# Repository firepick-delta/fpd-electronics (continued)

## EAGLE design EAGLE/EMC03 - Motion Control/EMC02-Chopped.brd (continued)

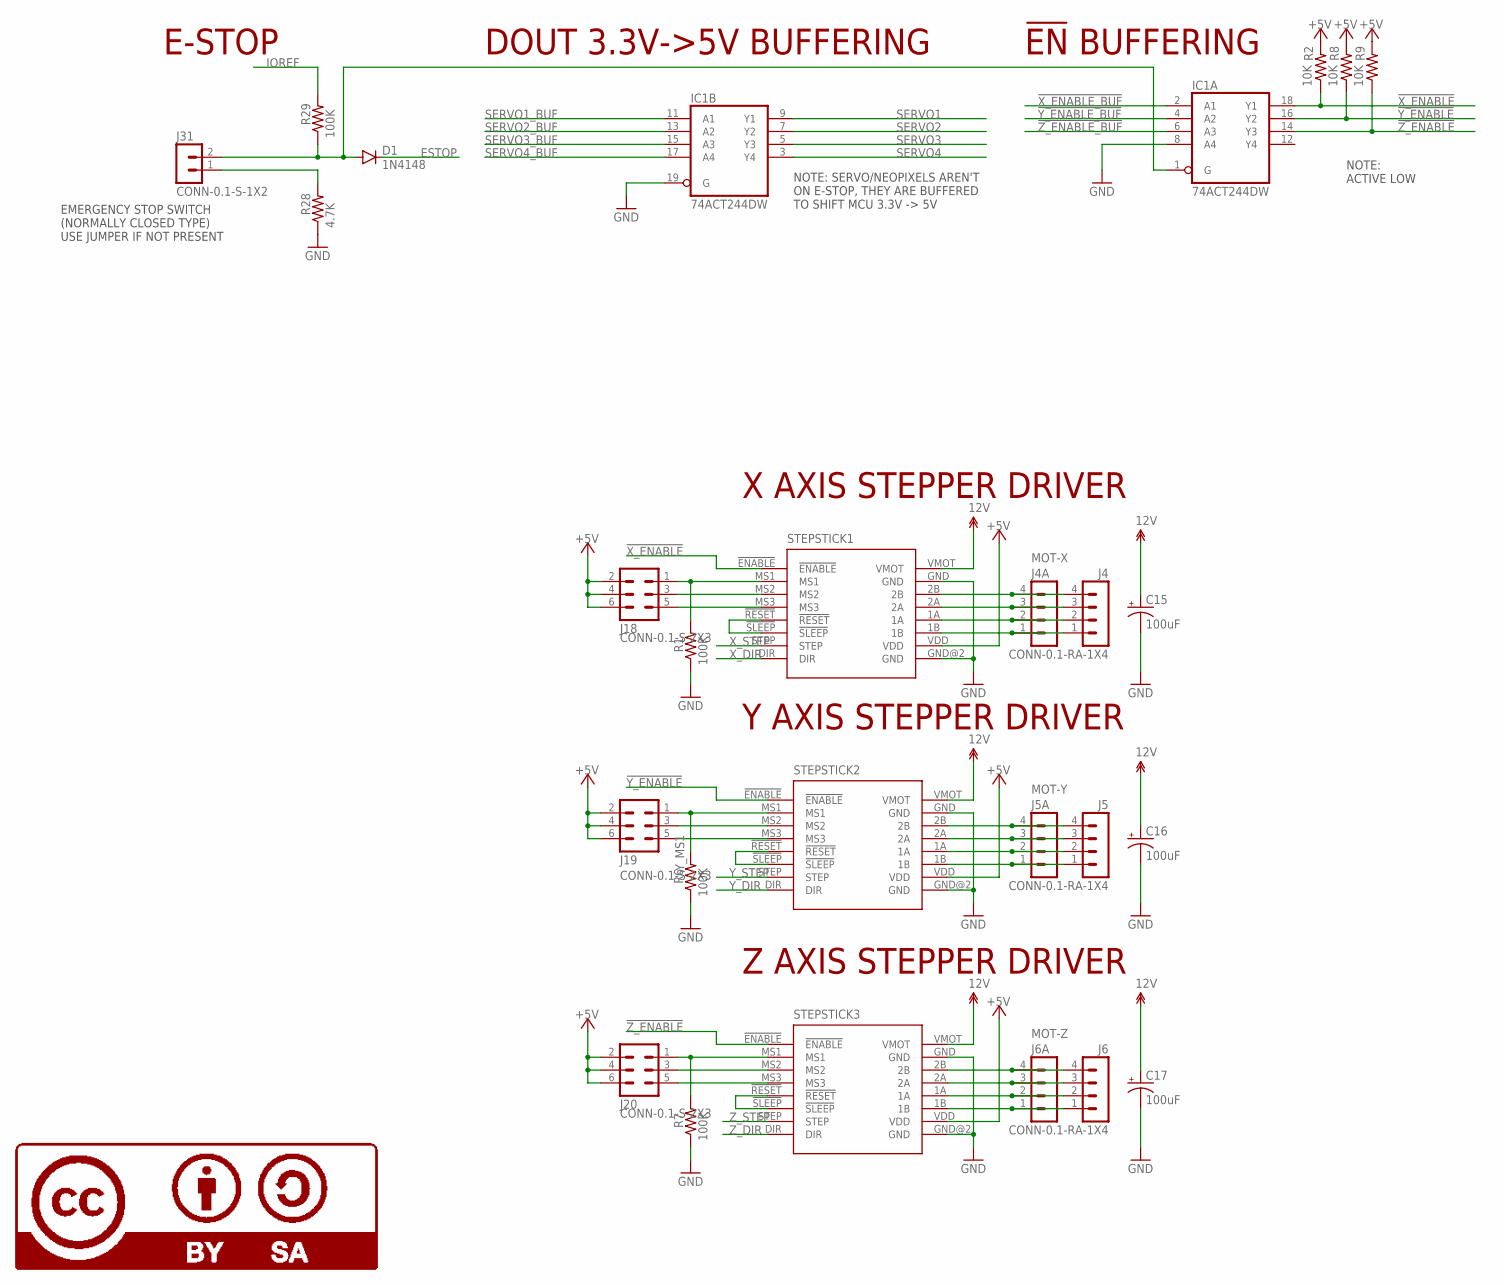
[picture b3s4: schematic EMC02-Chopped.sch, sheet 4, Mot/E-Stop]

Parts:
C15, C16, C17: 100uF; PANASONIC_D; PARTNO 25TXV100M6.3X8
D1: 1N4148; SOD-123; PARTNO 1N4148W-7-F
IC1: 74ACT244DW; SO20W; PARTNO 74ACT244SCX
J4, J5, J6: CONN-0.1-RA-1X4; MA04-1; PARTNO CONN-0.1-RA-1X4
J4A: MOT-X; CONN-JST-PH_2.0MM_4PIN-SMT-RA
J5A: MOT-Y; CONN-JST-PH_2.0MM_4PIN-SMT-RA
J6A: MOT-Z; CONN-JST-PH_2.0MM_4PIN-SMT-RA
J18, J19, J20: CONN-0.1-S-2X3; MA03-2; PARTNO CONN-0.1-S-2X3
J31: CONN-0.1-S-1X2; MA02-1; PARTNO CONN-0.1-S-1X2
LOGO7: LOGO-CC-BY-SALARGE; LOGO-CC-BY-SA
R1, R6, R7, R29: 100K; 0805; PARTNO RC0805FR-07100KL
R2, R8, R9: 10K; 0805; PARTNO RC0805FR-0710KL
R28: 4.7K; 0805; PARTNO RC0805FR-074K7L
STEPSTICK1, STEPSTICK2, STEPSTICK3: STEPSTICK; PARTNO PPPC081LFBN-RC

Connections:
12V: C15.+, C16.+, C17.+, STEPSTICK1.VMOT, STEPSTICK2.VMOT, STEPSTICK3.VMOT; also elsewhere on the board
!X_ENABLE: IC1.18 (Y1), R2.1, STEPSTICK1.!ENABLE!
!X_ENABLE_BUF: IC1.2 (A1)
!Y_ENABLE: IC1.16 (Y2), R8.1, STEPSTICK2.!ENABLE!
!Y_ENABLE_BUF: IC1.4 (A2)
!Z_ENABLE: IC1.14 (Y3), R9.1, STEPSTICK3.!ENABLE!
!Z_ENABLE_BUF: IC1.6 (A3)
+5V: J18.2, J18.4, J18.6, J19.2, J19.4, J19.6, J20.2, J20.4, J20.6, R2.2, R8.2, R9.2, STEPSTICK1.VDD, STEPSTICK2.VDD, STEPSTICK3.VDD; also elsewhere on the board
ESTOP: D1.C
ESTOP_OE: D1.A, IC1.1 (G), J31.2, R29.1
GND: C15.-, C16.-, C17.-, IC1.8 (A4), IC1.19 (G), R1.1, R6.1, R7.1, R28.1, STEPSTICK1.GND, STEPSTICK1.GND@2 (GND), STEPSTICK2.GND, STEPSTICK2.GND@2 (GND), STEPSTICK3.GND, STEPSTICK3.GND@2 (GND); also elsewhere on the board
IOREF: R29.2
unnamed: J31.1, R28.2
unnamed: STEPSTICK1.!RESET!, STEPSTICK1.!SLEEP!
unnamed: STEPSTICK2.!RESET!, STEPSTICK2.!SLEEP!
unnamed: STEPSTICK3.!RESET!, STEPSTICK3.!SLEEP!
SERVO1: IC1.9 (Y1); also elsewhere on the board
SERVO1_BUF: IC1.11 (A1)
SERVO2: IC1.7 (Y2); also elsewhere on the board
SERVO2_BUF: IC1.13 (A2)
SERVO3: IC1.5 (Y3); also elsewhere on the board
SERVO3_BUF: IC1.15 (A3)
SERVO4: IC1.3 (Y4); also elsewhere on the board
SERVO4_BUF: IC1.17 (A4)
X1A: J4.2, J4A.2, STEPSTICK1.1A
X1B: J4.1, J4A.1, STEPSTICK1.1B
X2A: J4.3, J4A.3, STEPSTICK1.2A
X2B: J4.4, J4A.4, STEPSTICK1.2B
X_DIR: STEPSTICK1.DIR
X_MS1: J18.1, R1.2, STEPSTICK1.MS1
X_MS2: J18.3, STEPSTICK1.MS2
X_MS3: J18.5, STEPSTICK1.MS3
X_STEP: STEPSTICK1.STEP
Y1A: J5.2, J5A.2, STEPSTICK2.1A
Y1B: J5.1, J5A.1, STEPSTICK2.1B
Y2A: J5.3, J5A.3, STEPSTICK2.2A
Y2B: J5.4, J5A.4, STEPSTICK2.2B
Y_DIR: STEPSTICK2.DIR
Y_MS1: J19.1, R6.2, STEPSTICK2.MS1
Y_MS2: J19.3, STEPSTICK2.MS2
Y_MS3: J19.5, STEPSTICK2.MS3
Y_STEP: STEPSTICK2.STEP
Z1A: J6.2, J6A.2, STEPSTICK3.1A
Z1B: J6.1, J6A.1, STEPSTICK3.1B
Z2A: J6.3, J6A.3, STEPSTICK3.2A
Z2B: J6.4, J6A.4, STEPSTICK3.2B
Z_DIR: STEPSTICK3.DIR
Z_MS1: J20.1, R7.2, STEPSTICK3.MS1
Z_MS2: J20.3, STEPSTICK3.MS2
Z_MS3: J20.5, STEPSTICK3.MS3
Z_STEP: STEPSTICK3.STEP

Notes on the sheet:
X AXIS STEPPER DRIVER
Y AXIS STEPPER DRIVER
Z AXIS STEPPER DRIVER
DOUT 3.3V->5V BUFFERING
EMERGENCY STOP SWITCH (NORMALLY CLOSED TYPE) USE JUMPER IF NOT PRESENT
E-STOP
!EN! BUFFERING
NOTE: ACTIVE LOW
NOTE: SERVO/NEOPIXELS AREN'T ON E-STOP, THEY ARE BUFFERED TO SHIFT MCU 3.3V -> 5V

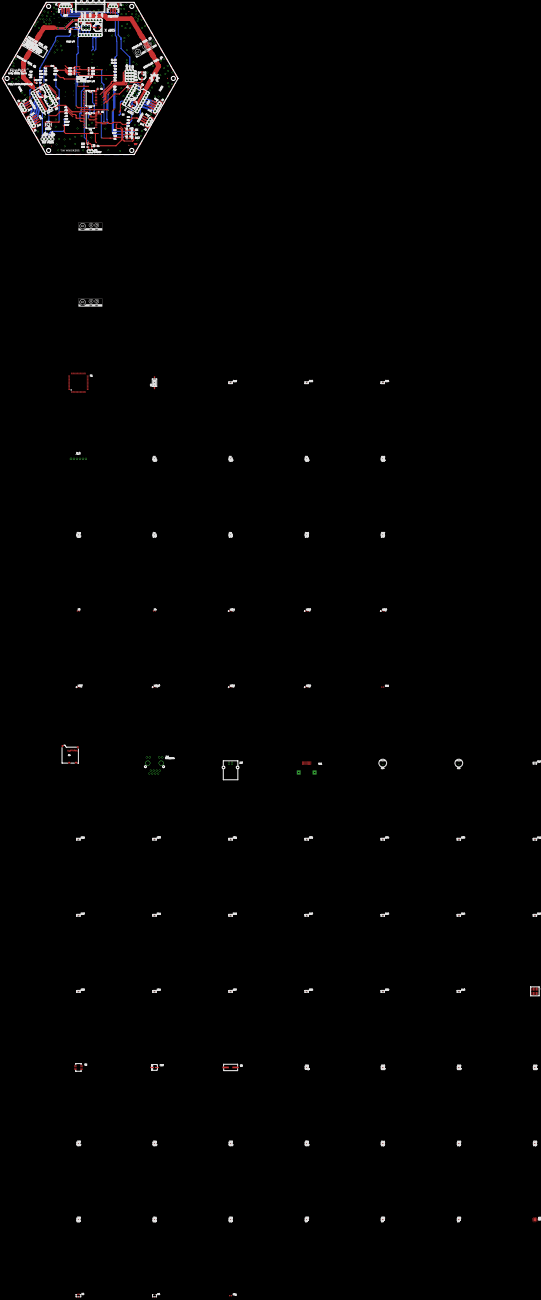
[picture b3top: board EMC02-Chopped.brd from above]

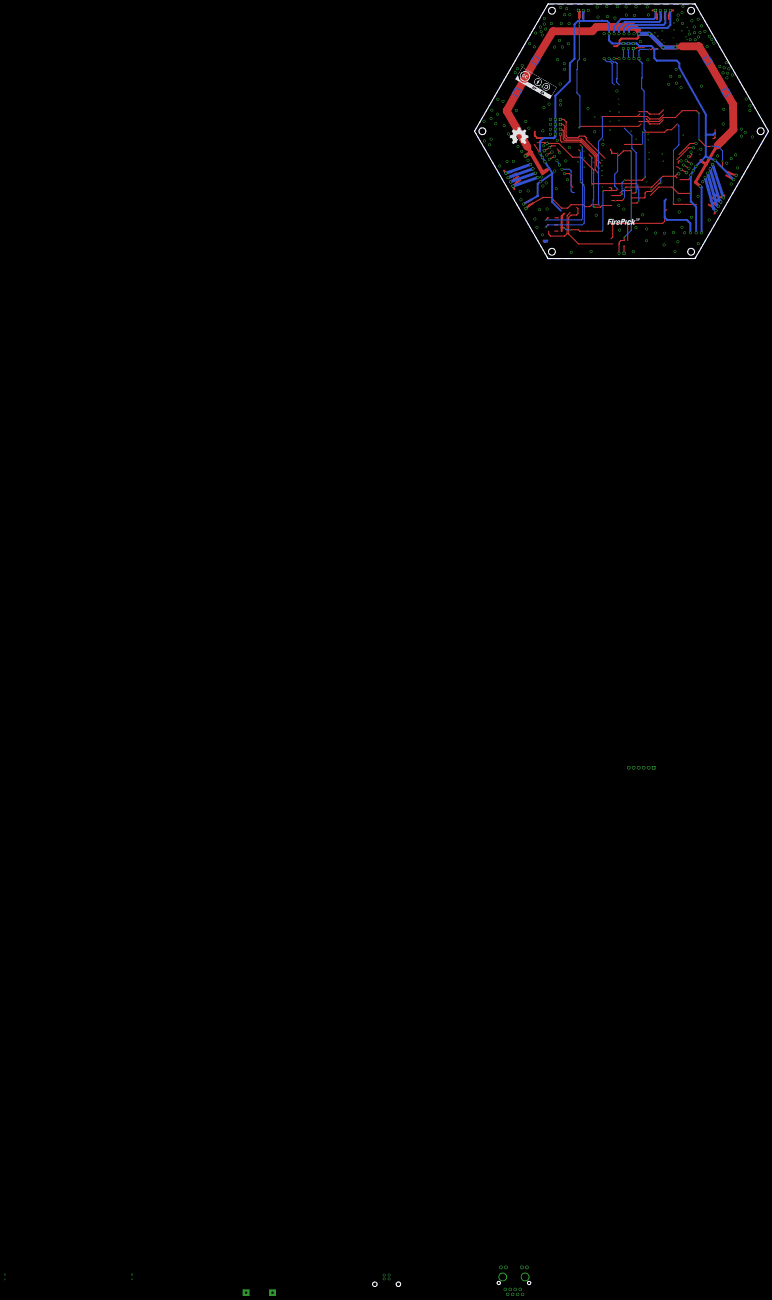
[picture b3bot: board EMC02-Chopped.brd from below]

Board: 4 copper layers, 150.0 x 129.9 mm, 152 parts (3 on the bottom side), 101 nets.

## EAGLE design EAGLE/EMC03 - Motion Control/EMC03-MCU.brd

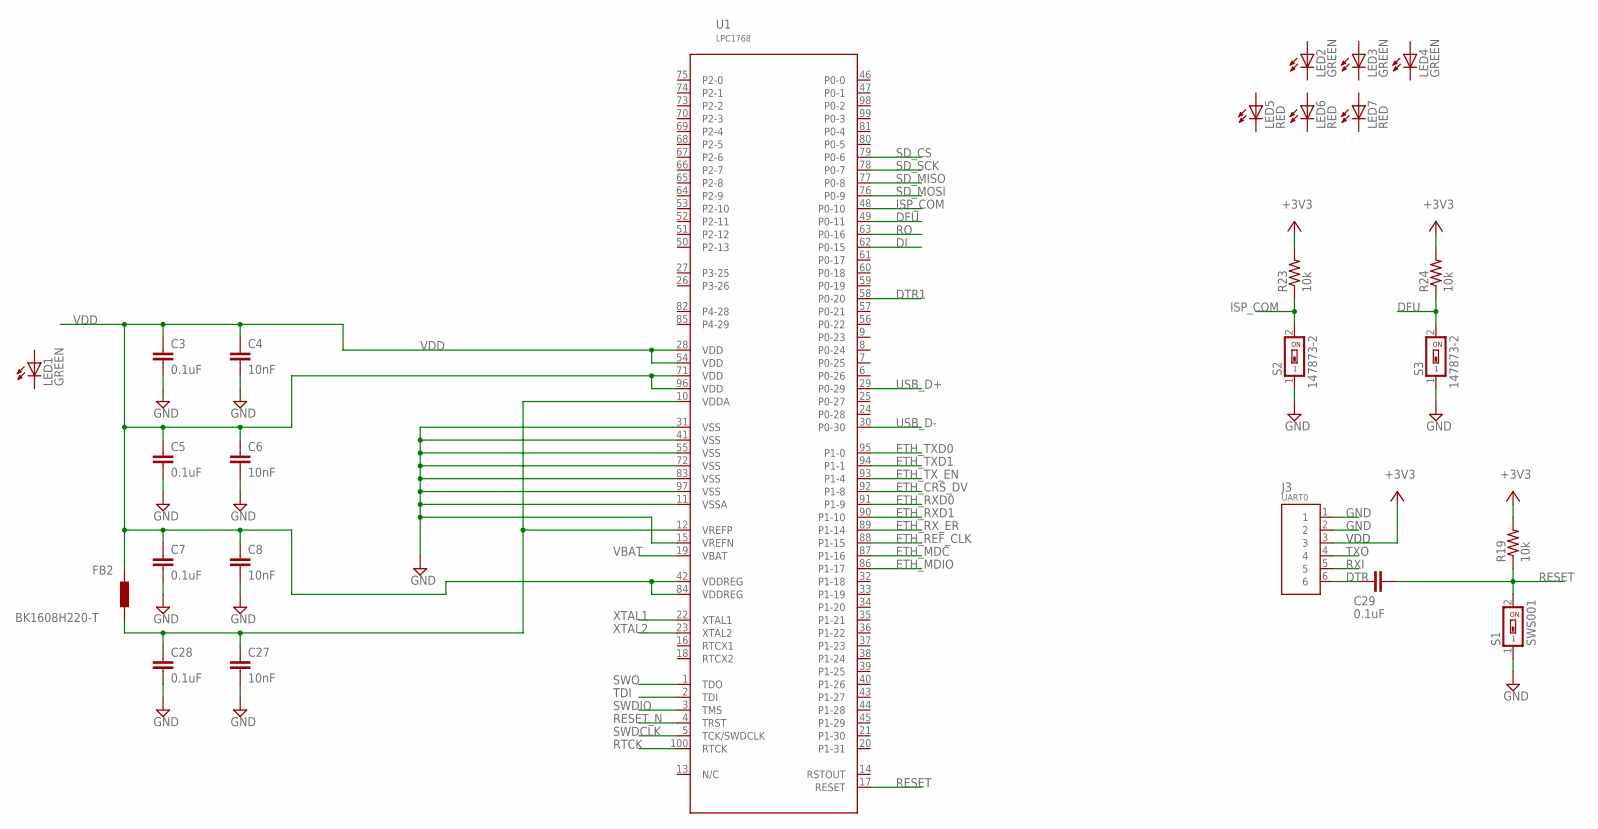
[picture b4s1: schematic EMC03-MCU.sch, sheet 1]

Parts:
C3, C5, C7, C28, C29: 0.1uF; C0603
C4, C6, C8, C27: 10nF; C0603
FB2: BK1608H220-T; F0603
J3: UART0; CON-HDR-6POS-MALE
LED1, LED2, LED3, LED4: GREEN; LED0603
LED5, LED6, LED7: RED; LED0603
R19, R23, R24: 10k; R0603
S1: SWS001; SMS-001
S2, S3: 147873-2; 0603
U1: LPC1768; LQFP-100

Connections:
+3V3: J3.3, R19.2, R23.2, R24.2; also elsewhere on the board
DFU: R24.1, S3.2, U1.49 (P0-11)
DI: U1.62 (P0-15); also elsewhere on the board
DTR: C29.1, J3.6
DTR1: U1.58 (P0-20); also elsewhere on the board
ETH_CRS_DV: U1.92 (P1-8); also elsewhere on the board
ETH_MDC: U1.87 (P1-16); also elsewhere on the board
ETH_MDIO: U1.86 (P1-17); also elsewhere on the board
ETH_REF_CLK: U1.88 (P1-15); also elsewhere on the board
ETH_RXD0: U1.91 (P1-9); also elsewhere on the board
ETH_RXD1: U1.90 (P1-10); also elsewhere on the board
ETH_RX_ER: U1.89 (P1-14); also elsewhere on the board
ETH_TXD0: U1.95 (P1-0); also elsewhere on the board
ETH_TXD1: U1.94 (P1-1); also elsewhere on the board
ETH_TX_EN: U1.93 (P1-4); also elsewhere on the board
GND: C3.1, C4.1, C5.1, C6.1, C7.1, C8.1, C28.1, J3.1, J3.2, S1.1, S2.1, S3.1, U1.11 (VSSA), U1.15 (VREFN), U1.31 (VSS), U1.41 (VSS), U1.55 (VSS), U1.72 (VSS), U1.83 (VSS), U1.97 (VSS); also elsewhere on the board
GND1: C27.1
ISP_COM: R23.1, S2.2, U1.48 (P0-10)
unnamed: C27.2, C28.2, FB2.1, U1.10 (VDDA), U1.12 (VREFP)
RESET: C29.2, R19.1, S1.2, U1.17 (RESET)
RESET_N: U1.4 (TRST); also elsewhere on the board
RO: U1.63 (P0-16); also elsewhere on the board
RTCK: U1.100 (RTCK); also elsewhere on the board
RXI: J3.5
SD_CS: U1.79 (P0-6); also elsewhere on the board
SD_MISO: U1.77 (P0-8); also elsewhere on the board
SD_MOSI: U1.76 (P0-9); also elsewhere on the board
SD_SCK: U1.78 (P0-7); also elsewhere on the board
SWDCLK: U1.5 (TCK/SWDCLK); also elsewhere on the board
SWDIO: U1.3 (TMS); also elsewhere on the board
SWO: U1.1 (TDO); also elsewhere on the board
TDI: U1.2 (TDI); also elsewhere on the board
TXO: J3.4
USB_D+: U1.29 (P0-29); also elsewhere on the board
USB_D-: U1.30 (P0-30); also elsewhere on the board
VBAT: U1.19 (VBAT)
VDD: C3.2, C4.2, C5.2, C6.2, C7.2, C8.2, FB2.2, U1.28 (VDD), U1.42 (VDDREG), U1.54 (VDD), U1.71 (VDD), U1.84 (VDDREG), U1.96 (VDD)
XTAL1: U1.22 (XTAL1); also elsewhere on the board
XTAL2: U1.23 (XTAL2); also elsewhere on the board

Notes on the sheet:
VDD

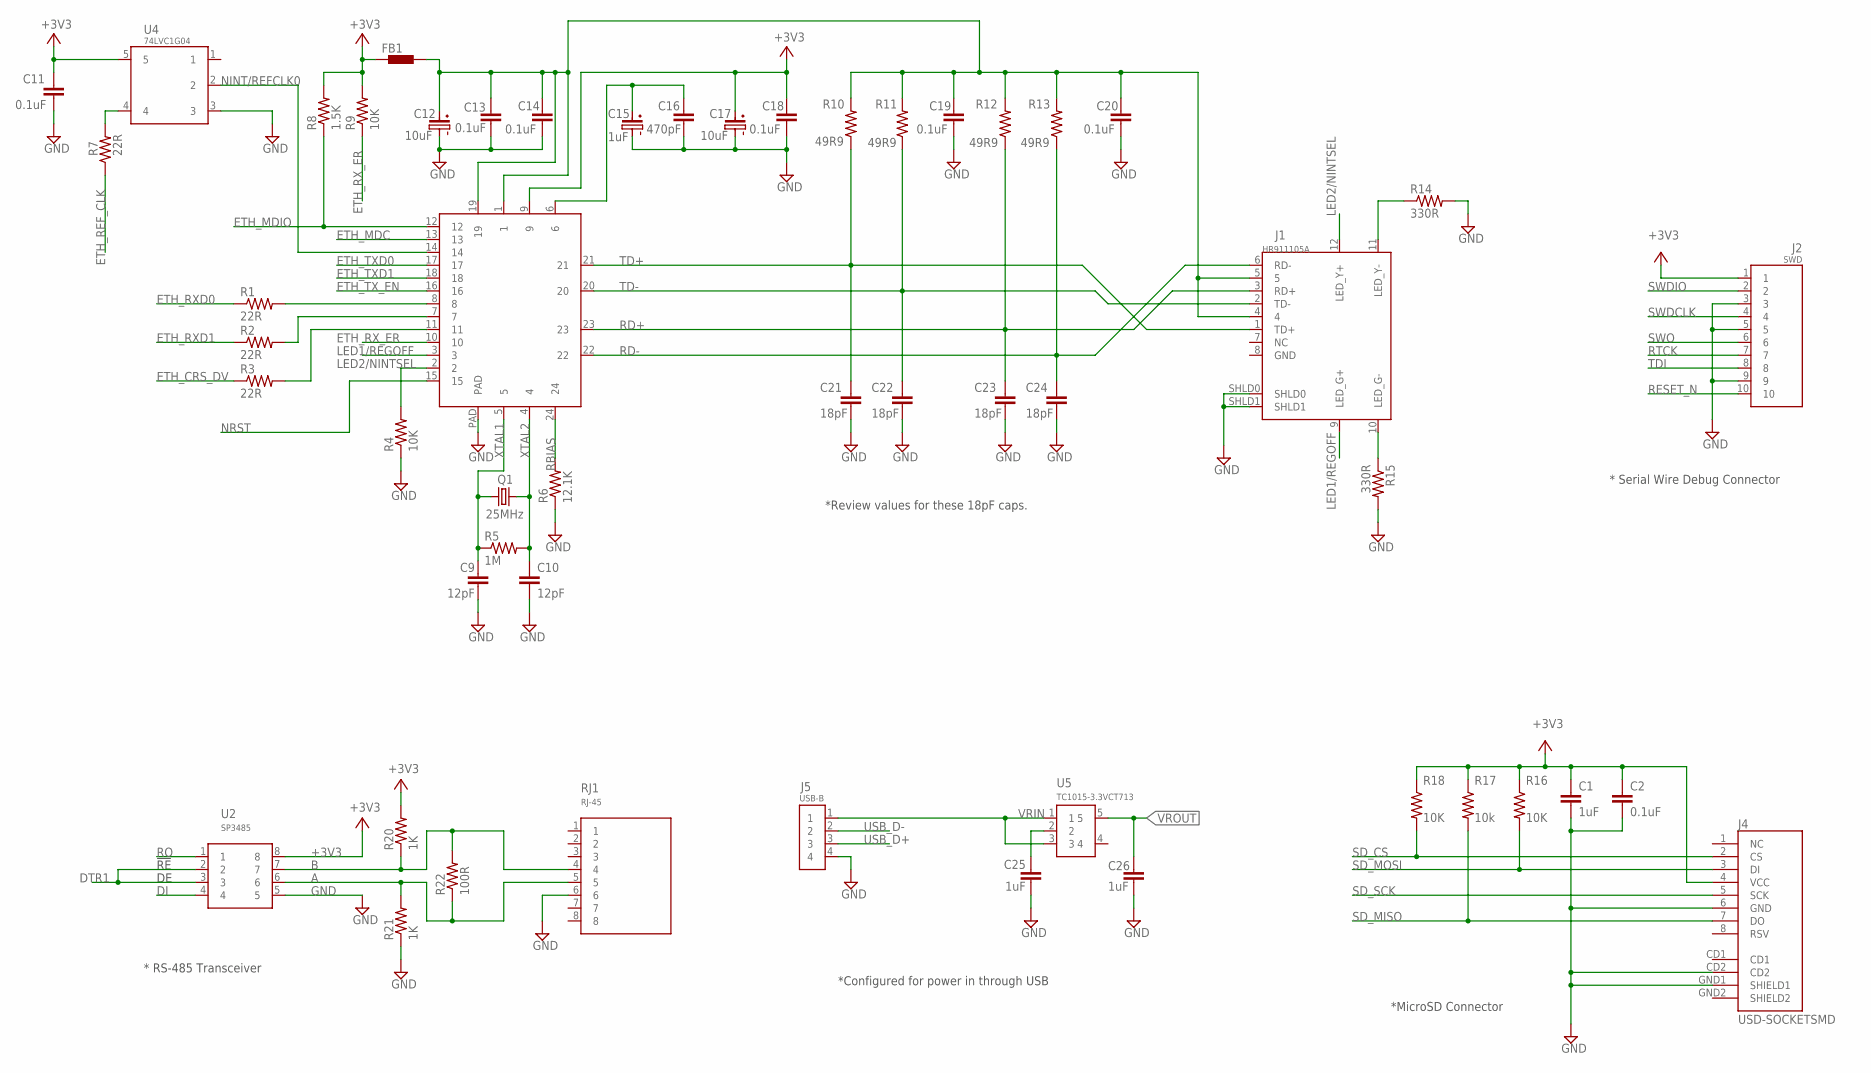
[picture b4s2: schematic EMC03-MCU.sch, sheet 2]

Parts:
C1, C25, C26: 1uF; C0603
C2, C11, C13, C14, C18, C19, C20: 0.1uF; C0603
C9, C10: 12pF; C0603
C12, C17: 10uF; C-RAD-6.3MM
C15: 1uF; C-SMD-4MM
C16: 470pF; C0603
C21, C22, C23, C24: 18pF; C0603
FB1: BLM15HBK1608H220-T0603; F0603
J1: HR911105A; MAGJACK(HR911105A)
J2: SWD; FTSH-105-01-XXX-DV-K
J4: USD-SOCKETSMD; MICRO-SD-SOCKET-PP
J5: USB-B; USB-B(THRU)
Q1: 25MHz; HC-49/U-S
R1, R2, R3, R7: 22R; R0603
R4, R9, R16, R18: 10K; R0603
R5: 1M; R0603
R6: 12.1K; R0603
R8: 1.5K; R0603
R10, R11, R12, R13: 49R9; R0603
R14, R15: 330R; R0603
R17: 10k; R0603
R20, R21: 1K; R0603
R22: 100R; R0603
RJ1: RJ-45; CON-RJ45
U2: SP3485; SOICN-8
U3: CPL-ETH-PHY-LAN8720A; QFN-24
U4: 74LVC1G04; SOT-25
U5: TC1015-3.3VCT713; SOT-23-5

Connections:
+3V3: C1.2, C2.2, C11.2, C17.POS, C18.2, FB1.1, J2.1, J4.4 (VCC), R8.2, R9.2, R16.1, R17.1, R18.1, R20.2, U2.8, U3.9, U4.5; also elsewhere on the board
A: R21.2, R22.1, RJ1.5, U2.6
B: R20.1, R22.2, RJ1.4, U2.7
DI: U2.4; also elsewhere on the board
DTR1: U2.2, U2.3; also elsewhere on the board
ETH_CRS_DV: R3.1; also elsewhere on the board
ETH_MDC: U3.13; also elsewhere on the board
ETH_MDIO: R8.1, U3.12; also elsewhere on the board
ETH_REF_CLK: R7.1; also elsewhere on the board
ETH_RXD0: R1.1; also elsewhere on the board
ETH_RXD1: R2.1; also elsewhere on the board
ETH_RX_ER: R9.1, U3.10; also elsewhere on the board
ETH_TXD0: U3.17; also elsewhere on the board
ETH_TXD1: U3.18; also elsewhere on the board
ETH_TX_EN: U3.16; also elsewhere on the board
GND: C1.1, C2.1, C9.1, C10.1, C11.1, C12.NEG, C13.1, C14.1, C15.NEG, C16.1, C17.NEG, C18.1, C19.1, C20.1, C21.1, C22.1, C23.1, C24.1, C25.1, C26.1, J1.SHLD0, J1.SHLD1, J2.3, J2.5, J2.9, J4.6 (GND), J4.CD2, J4.GND1 (SHIELD1), J5.4, R4.1, R6.1, R14.2, R15.2, R21.1, RJ1.6, U2.5, U3.PAD, U4.3; also elsewhere on the board
LED1/REGOFF: J1.9 (LED_G+), U3.3
LED2/NINTSEL: J1.12 (LED_Y+), R4.2, U3.2
unnamed: J1.11 (LED_Y-), R14.1
unnamed: J1.10 (LED_G-), R15.1
unnamed: R1.2, U3.8
unnamed: C25.2, U5.2
unnamed: R2.2, U3.7
unnamed: R3.2, U3.11
unnamed: R7.2, U4.4
unnamed: C12.POS, C13.2, C14.2, C19.2, C20.2, FB1.2, J1.4, J1.5, R10.2, R11.2, R12.2, R13.2, U3.1, U3.19
unnamed: C15.POS, C16.2, U3.6
NINT/REFCLK0: U3.14, U4.2
NRST: U3.15
RBIAS: R6.2, U3.24
RD+: C23.2, J1.3 (RD+), R12.1, U3.23
RD-: C24.2, J1.6 (RD-), R13.1, U3.22
RESET_N: J2.10; also elsewhere on the board
RO: U2.1; also elsewhere on the board
RTCK: J2.7; also elsewhere on the board
SD_CS: J4.2 (CS), R18.2; also elsewhere on the board
SD_MISO: J4.7 (DO), R17.2; also elsewhere on the board
SD_MOSI: J4.3 (DI), R16.2; also elsewhere on the board
SD_SCK: J4.5 (SCK); also elsewhere on the board
SWDCLK: J2.4; also elsewhere on the board
SWDIO: J2.2; also elsewhere on the board
SWO: J2.6; also elsewhere on the board
TD+: C21.2, J1.1 (TD+), R10.1, U3.21
TD-: C22.2, J1.2 (TD-), R11.1, U3.20
TDI: J2.8; also elsewhere on the board
USB_D+: J5.3; also elsewhere on the board
USB_D-: J5.2; also elsewhere on the board
VRIN: J5.1, U5.1, U5.3
VROUT: C26.2, U5.5
XTAL1: C9.2, Q1.1, R5.1, U3.5; also elsewhere on the board
XTAL2: C10.2, Q1.2, R5.2, U3.4; also elsewhere on the board

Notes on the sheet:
*Configured for power in through USB
*Review values for these 18pF caps.
*MicroSD Connector
!RE
* Serial Wire Debug Connector
* RS-485 Transceiver

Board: 4 copper layers, 77 parts (0 on the bottom side), 56 nets, no tracks yet.
